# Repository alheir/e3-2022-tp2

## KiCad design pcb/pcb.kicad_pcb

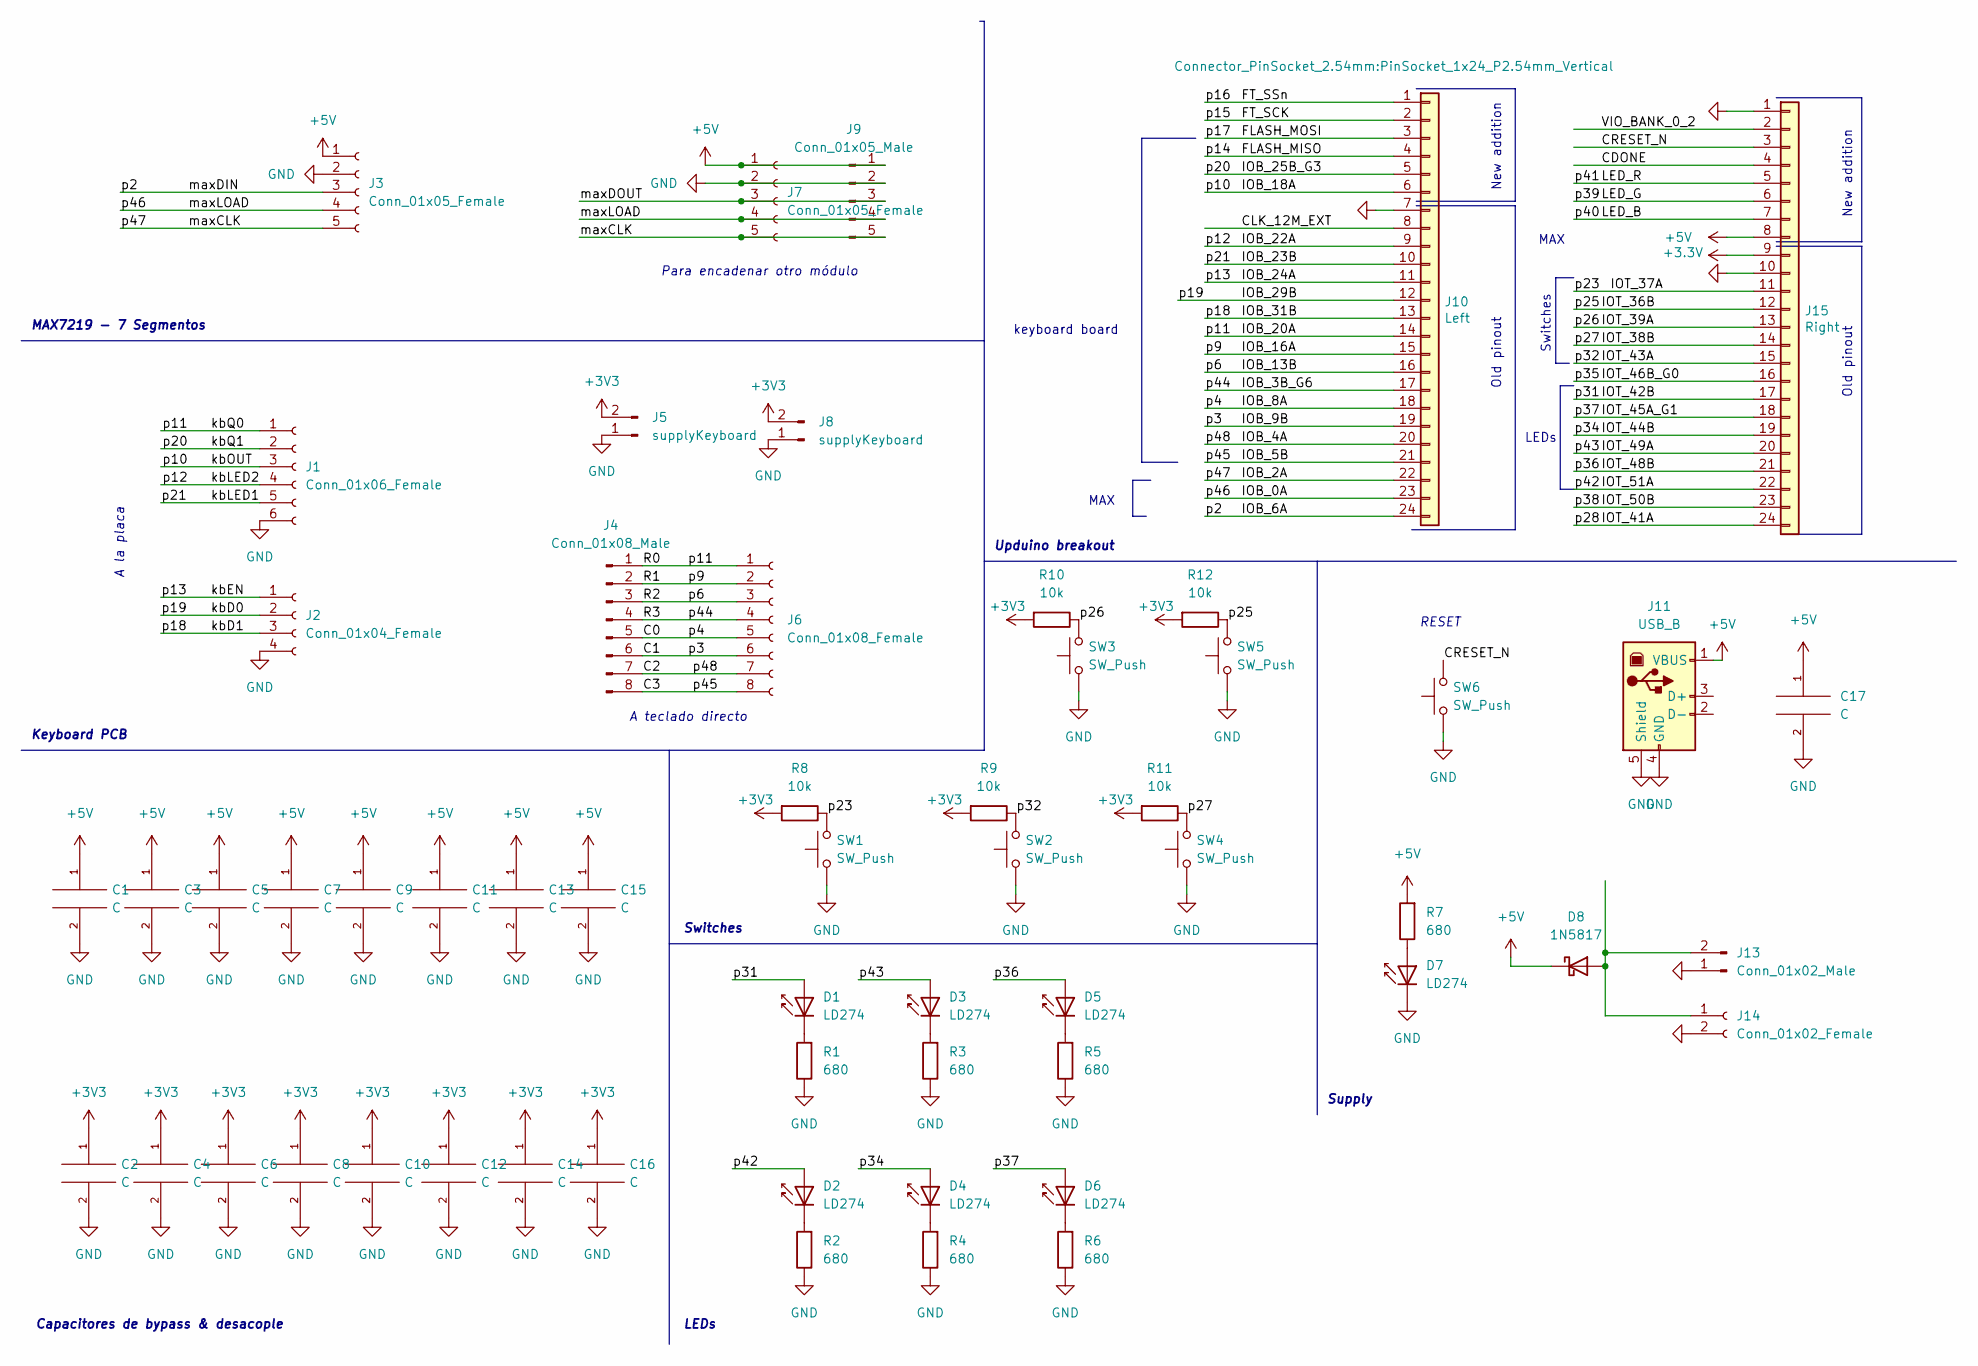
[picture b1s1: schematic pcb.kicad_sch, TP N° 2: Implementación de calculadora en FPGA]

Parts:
C1, C2, C3, C4, C5, C6, C7, C8, C9, C10, C11, C12, C13, C14, C15, C16: C; C_0805_2012Metric
C17: C; C_Disc_D8.0mm_W2.5mm_P5.00mm
D1, D2, D3, D4, D5, D6, D7: LD274; LED_D5.0mm_IRGrey
D8: 1N5817; D_DO-41_SOD81_P10.16mm_Horizontal
J1: Conn_01x06_Female; PinHeader_1x06_P2.54mm_Vertical
J2: Conn_01x04_Female; PinHeader_1x04_P2.54mm_Vertical
J3: Conn_01x05_Female; PinSocket_1x05_P2.54mm_Vertical
J4: Conn_01x08_Male; PinHeader_1x08_P2.54mm_Vertical
J5: supplyKeyboard; PinHeader_1x02_P2.54mm_Vertical
J6: Conn_01x08_Female; PinSocket_1x08_P2.54mm_Vertical
J7: Conn_01x05_Female; PinHeader_1x05_P2.54mm_Vertical
J8: supplyKeyboard; PinSocket_1x02_P2.54mm_Vertical
J9: Conn_01x05_Male; PinSocket_1x05_P2.54mm_Vertical
J10: Left; PinSocket_1x24_P2.54mm_Vertical
J11: USB_B; USB_B_OST_USB-B1HSxx_Horizontal
J13: Conn_01x02_Male; PinSocket_1x02_P2.54mm_Vertical
J14: Conn_01x02_Female; PinSocket_1x02_P2.54mm_Vertical
J15: Right; PinSocket_1x24_P2.54mm_Vertical
R1, R2, R3, R4, R5, R6, R7: 680; R_0805_2012Metric
R8, R9, R10, R11, R12: 10k; R_0805_2012Metric
SW1, SW2, SW3, SW4, SW5, SW6: SW_Push; SW_PUSH_6mm

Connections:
+5V: C1.1, C3.1, C5.1, C7.1, C9.1, C11.1, C13.1, C15.1, C17.1, D8.1 (K), J3.1, J7.1, J9.1, J11.1 (VBUS), J15.8, R7.2
/C0: J4.5, J6.5, J10.18
/C1: J4.6, J6.6, J10.19
/C2: J4.7, J6.7, J10.20
/C3: J4.8, J6.8, J10.21
/CDONE: J15.4
/CLK_12M_EXT: J10.8
/CRESET_N: J15.3, SW6.2
/FLASH_MISO: J10.4
/FLASH_MOSI: J10.3
/FT_SCK: J10.2
/FT_SSn: J10.1
/IOB_0A: J3.4, J7.4, J9.4, J10.23
/IOB_2A: J3.5, J7.5, J9.5, J10.22
/IOB_3B_G6: J4.4, J6.4, J10.17
/IOB_6A: J3.3, J10.24
/IOB_13B: J4.3, J6.3, J10.16
/IOB_16A: J4.2, J6.2, J10.15
/IOB_18A: J1.3, J10.6
/IOB_20A: J1.1, J4.1, J6.1, J10.14
/IOB_22A: J1.4, J10.9
/IOB_23B: J1.5, J10.10
/IOB_24A: J2.1, J10.11
/IOB_25B_G3: J1.2, J10.5
/IOB_29B: J2.2, J10.12
/IOB_31B: J2.3, J10.13
/IOT_36B: J15.12, R12.1, SW5.2
/IOT_37A: J15.11, R8.1, SW1.2
/IOT_38B: J15.14, R11.1, SW4.2
/IOT_39A: J15.13, R10.1, SW3.2
/IOT_41A: J15.24
/IOT_42B: D1.2 (A), J15.17
/IOT_43A: J15.15, R9.1, SW2.2
/IOT_44B: D4.2 (A), J15.19
/IOT_45A_G1: D6.2 (A), J15.18
/IOT_46B_G0: J15.16
/IOT_48B: D5.2 (A), J15.21
/IOT_49A: D3.2 (A), J15.20
/IOT_50B: J15.23
/IOT_51A: D2.2 (A), J15.22
/LED_B: J15.7
/LED_G: J15.6
/LED_R: J15.5
/VIO_BANK_0_2: J15.2
/maxDOUT: J7.3, J9.3
GND: C1.2, C2.2, C3.2, C4.2, C5.2, C6.2, C7.2, C8.2, C9.2, C10.2, C11.2, C12.2, C13.2, C14.2, C15.2, C16.2, C17.2, D7.1 (K), J1.6, J2.4, J3.2, J5.1, J7.2, J8.1, J9.2, J10.7, J11.4 (GND), J11.5 (Shield), J13.1, J14.2, J15.1, J15.10, R1.1, R2.1, R3.1, R4.1, R5.1, R6.1, SW1.1, SW2.1, SW3.1, SW4.1, SW5.1, SW6.1
unnamed: D1.1 (K), R1.2
unnamed: D2.1 (K), R2.2
unnamed: D3.1 (K), R3.2
unnamed: D4.1 (K), R4.2
unnamed: D5.1 (K), R5.2
unnamed: D6.1 (K), R6.2
unnamed: D7.2 (A), R7.1
unnamed: D8.2 (A), J13.2, J14.1

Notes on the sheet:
A teclado directo
MAX
A la placa
LEDs
Old pinout
Capacitores de bypass & desacople
LEDs
Para encadenar otro módulo
Upduino breakout
Supply
MAX7219 - 7 Segmentos
New addition
Switches
keyboard board
RESET
Keyboard PCB

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
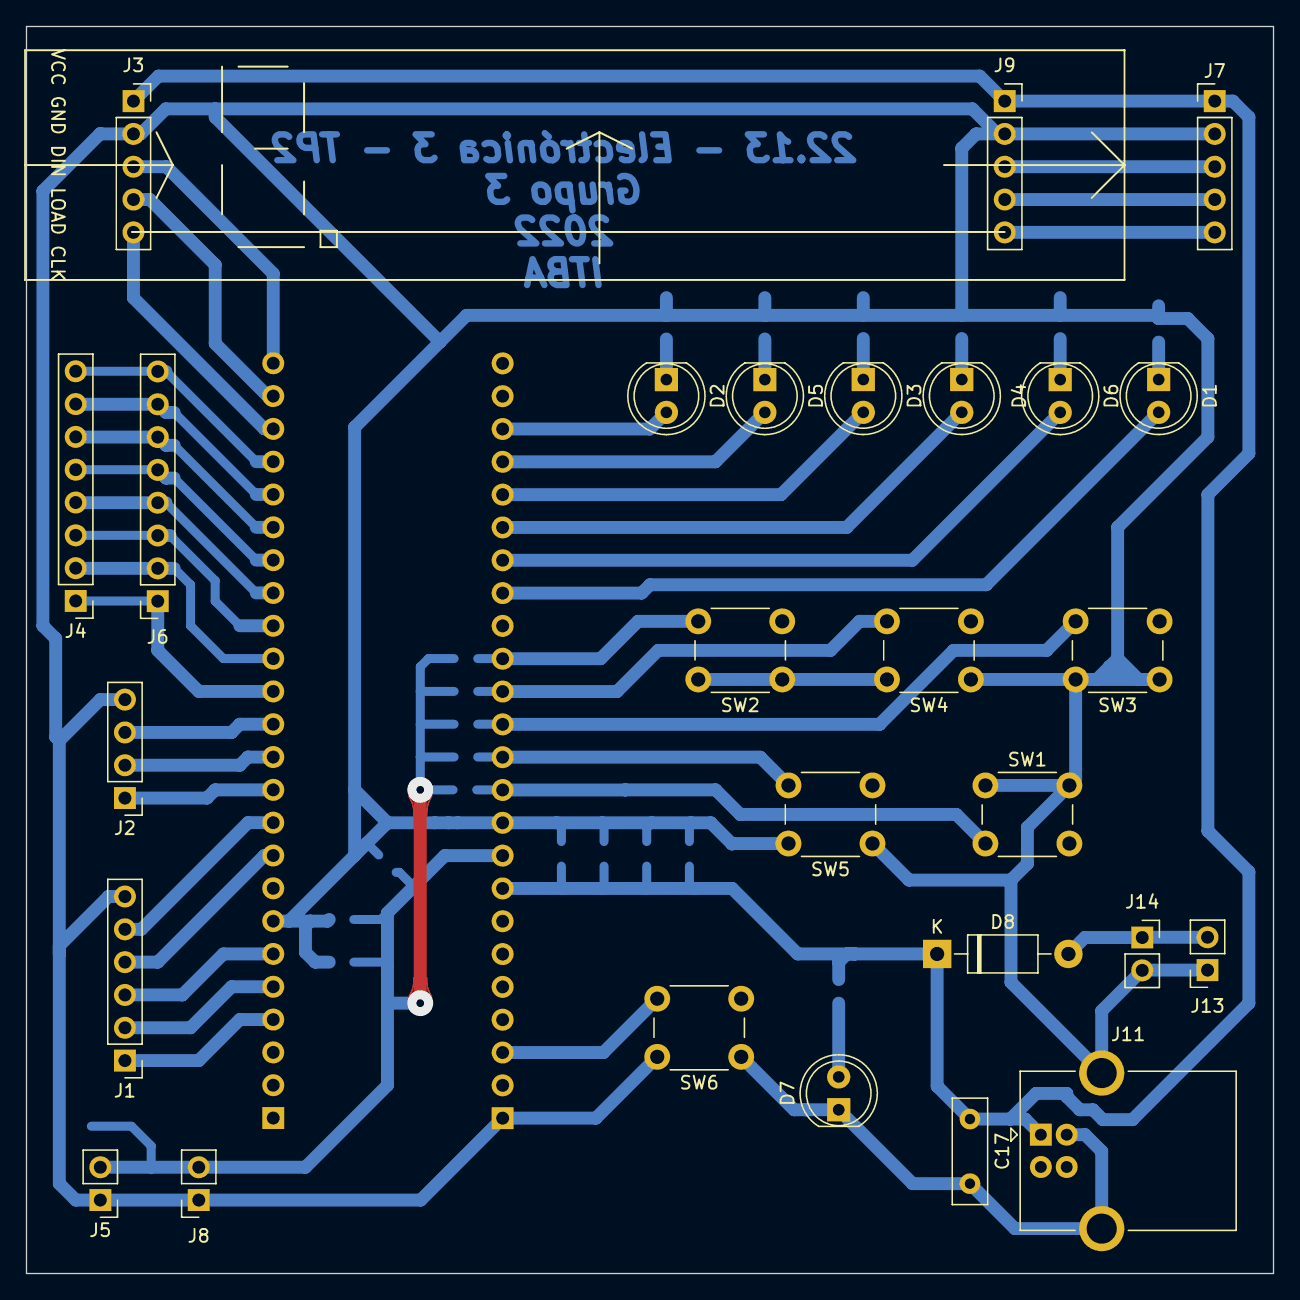
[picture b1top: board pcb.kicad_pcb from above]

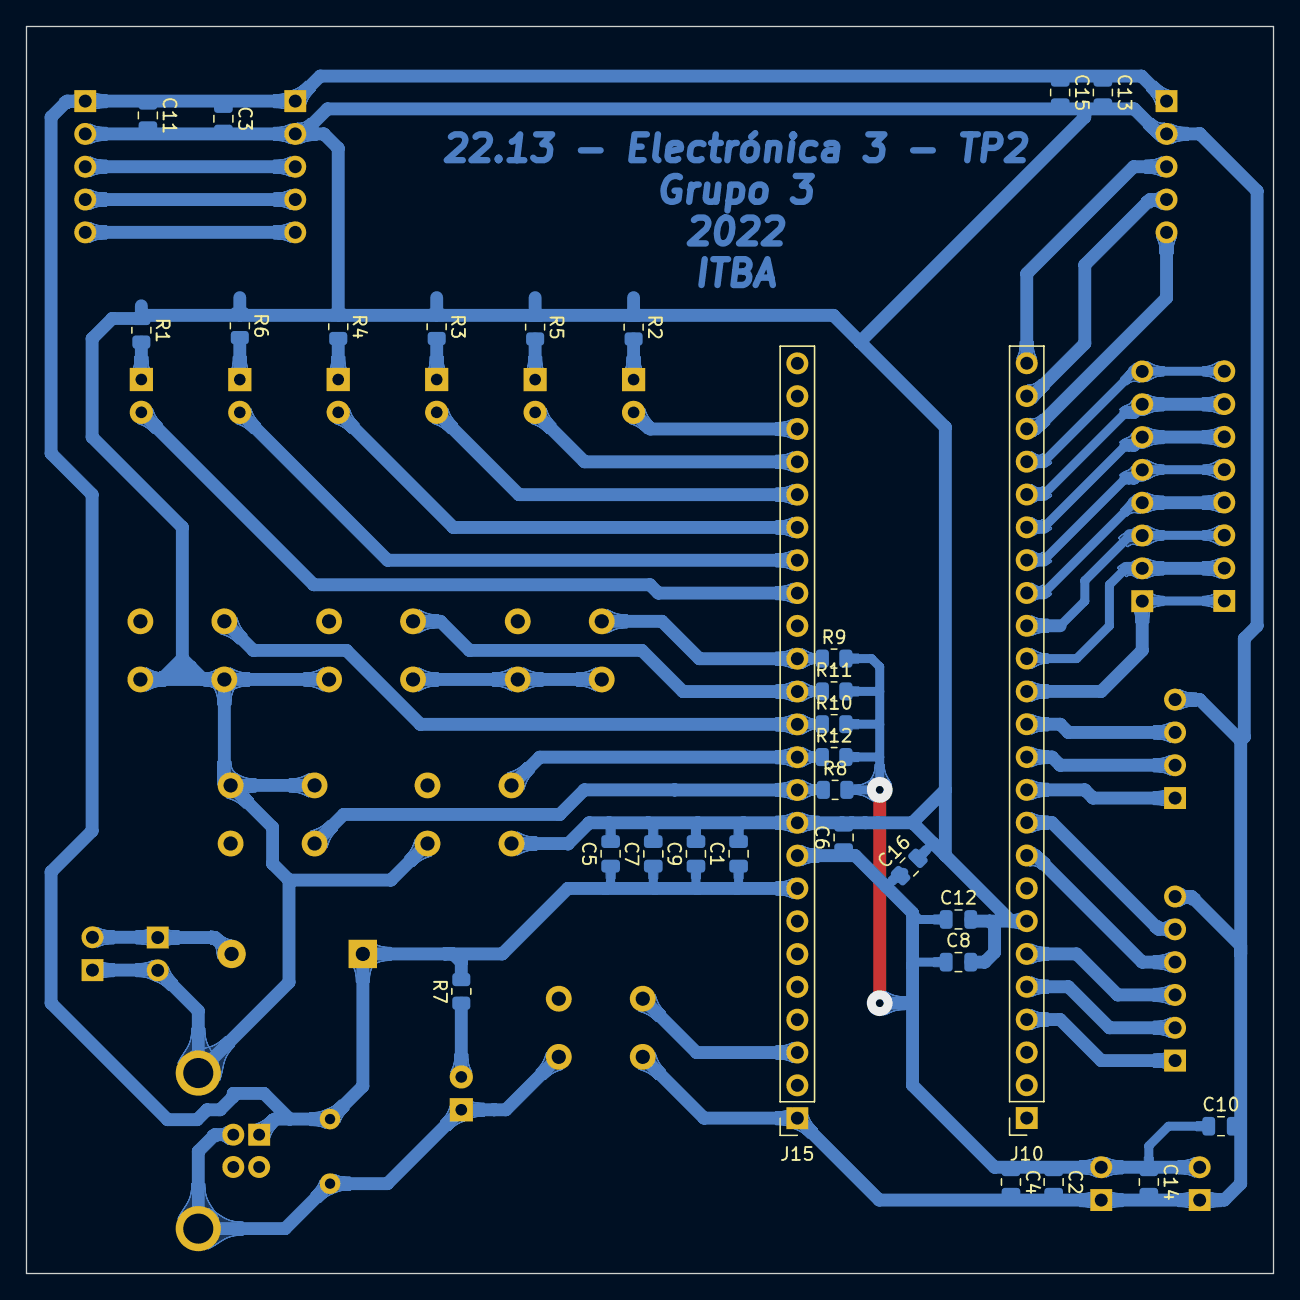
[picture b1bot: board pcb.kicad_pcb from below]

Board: 2 copper layers, 96.5 x 96.5 mm, 57 parts (30 on the bottom side), 42 nets.

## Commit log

2022-10-31 consigna
2022-10-31 testing upduinov3 con makefile
2022-10-31 alpha file structure
2022-10-31 activehdl empty files
2022-11-24 PCB ready, y testeos de MAX7219
2022-11-24 main display ??
2022-11-24 Agrego pcb, agrego fsm
2022-11-24 Conexión fsm-display
2022-11-24 main v2
2022-11-24 param codes
2022-11-24 Agrego cambios
2022-11-24 unificando modulos
2022-11-24 no warnings thus far
2022-11-24 back dispplay
2022-11-24 Beautificación ALU, mejora fsm, integración
2022-11-24 some of codes to display
2022-11-24 backup prev Franco alu update
2022-11-27 ajustes de la la noche de la presentacion fallida
2022-11-27 kicad backups
2022-11-27 control aceptable del display (independiente)
2022-11-27 prescaler adicional para display
2022-11-28 suma, resta, negativos, cociente, encadenación
2022-11-28 Cambios dp
2022-11-28 cosas
2022-11-28 fix multiplicacion, ajustes display
2022-11-29 versión presentada (brillo, dp, dual clock, fix bouncing)
2022-11-29 pos fixes pcb kicad
2022-11-29 kicad pdfs to report
2022-11-29 upduino makefile template byGullino
2022-11-29 more kicad backups
2022-12-01 report stuff (diagrams, pics, etc.)
2022-12-01 informe y consigna (PDF)
2022-12-01 repo refresh
2022-12-01 makefile flush
2022-12-01 unhide src gitignore
